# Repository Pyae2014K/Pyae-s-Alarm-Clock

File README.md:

# Pyae-s-Alarm-Clock

My alarm clock is an alarm clock with 6 keys, a TFT screen, and a buzzer.

It serves as an alarm clock that I can use every day to wake up on time for school.

## Features:
- 2.25in TFT Screen
- Buzzer for alarm
- 6 keys to do alarm things

## CAD Model
Everything fits together using 8 M3 Bolts and heatset inserts.

It has 2 different pieces, the Case and the Plate.

The model was made in Shapr 3D

##PCB
My PCB was made using KiCad
Schematic

PCB

I used the footprints that were shown in the guide.

## Firmware
This alarm clock uses Arduino IDE
It does alarm clock things.

## BOM:
Here is everything you will need to make this alarm clock

6x Charry MX Switches
6x DSA Keycaps
8x M3x5x4 Heatset inserts
8x M3x16mm SHCS Bolts
6x 1N4148 DO-35 Diodes.
1x 2.25in TFT Screen
1x XIAO ESP32C3
1x Case (2 printed parts)

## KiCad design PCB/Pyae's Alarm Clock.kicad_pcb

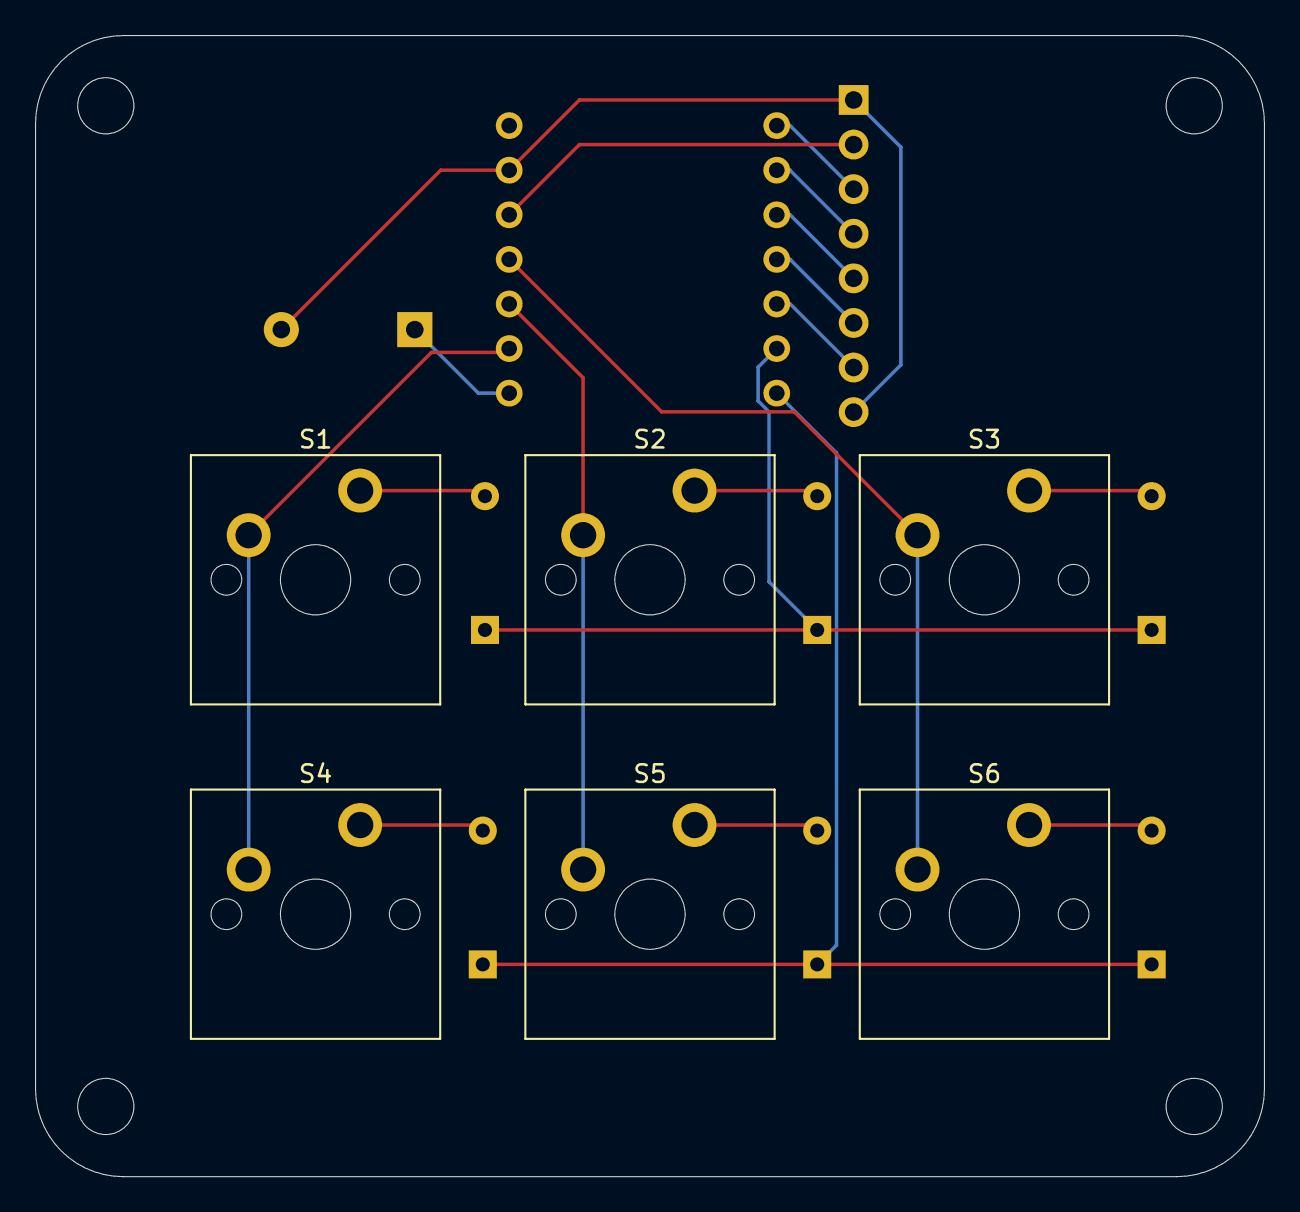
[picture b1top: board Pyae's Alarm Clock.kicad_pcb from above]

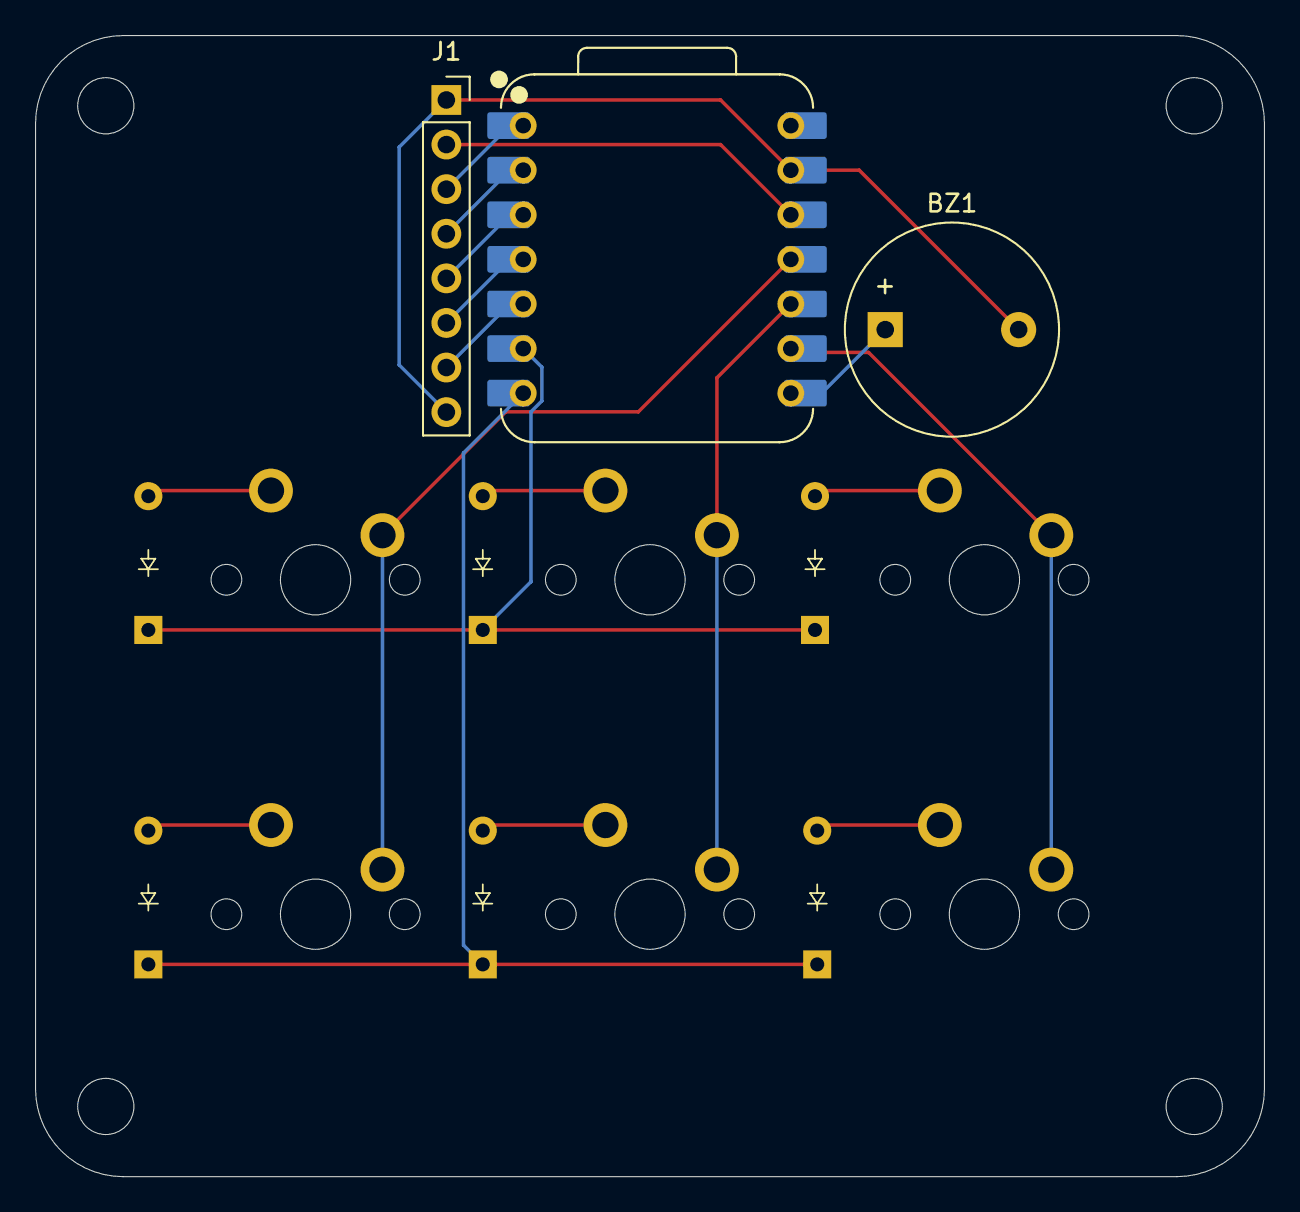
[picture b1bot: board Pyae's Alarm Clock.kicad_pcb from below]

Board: 2 copper layers, 70.0 x 65.0 mm, 19 parts (9 on the bottom side), 19 nets.

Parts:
BZ1: Buzzer; Buzzer_12x9.5RM7.6
D1, D2, D3, D4, D5, D6: Diode_DO-35
H1, H2, H3, H4: MountingHole; MountingHole_3.2mm_M3
J1: Conn_01x08_Pin; PinSocket_1x08_P2.54mm_Vertical
S1, S2, S3, S4, S5, S6: MX_PCB_1.00u
U1: XIAO-ESP32-C3-SMD; XIAO-ESP32-C3-DIP

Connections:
+3.3V: J1.2, U1.12 (3V3_OUT)
/CS: J1.7, U1.5 (D4)
/Col0: S1.1, S4.1, U1.9 (D8)
/Col1: S2.1, S5.1, U1.10 (D9/BOOT)
/Col2: S3.1, S6.1, U1.11 (D10)
/DC: J1.6, U1.4 (D3)
/RST: J1.5, U1.3 (D2)
/Row0: D1.1 (K), D2.1 (K), D3.1 (K), U1.6 (D5)
/Row1: D4.1 (K), D5.1 (K), D6.1 (K), U1.7 (D6)
/SCL: J1.3, U1.1 (D0)
/SDA: J1.4, U1.2 (D1)
GND: BZ1.2 (-), J1.1, J1.8, U1.13 (GND)
unnamed: BZ1.1 (+), U1.8 (D7)
unnamed: D1.2 (A), S1.2
unnamed: D2.2 (A), S2.2
unnamed: D3.2 (A), S3.2
unnamed: D4.2 (A), S4.2
unnamed: D5.2 (A), S5.2
unnamed: D6.2 (A), S6.2

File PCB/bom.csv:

Designator,Footprint,Quantity,Value,LCSC Part #
BZ1,Buzzer_12x9.5RM7.6,1,Buzzer,
"D1, D2, D3, D4, D5, D6",Diode_DO-35,6,~,
J1,PinSocket_1x08_P2.54mm_Vertical,1,Conn_01x08_Pin,
"S1, S2, S3, S4, S5, S6",MX_PCB_1.00u,6,~,
U1,XIAO-ESP32-C3-DIP,1,XIAO-ESP32-C3-SMD,

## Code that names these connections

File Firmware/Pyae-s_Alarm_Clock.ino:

#include <Adafruit_GFX.h>
#include <Adafruit_ST7789.h>
#include <SPI.h>
#include <WiFi.h>
#include "time.h"

const char* ssid = "your-wifi-name";
const char* password = "your-wifi-password";

// --- Display pins ---
#define TFT_SCLK 0
#define TFT_MOSI 1
#define TFT_RST 2
#define TFT_DC 3
#define TFT_CS 4
// BL hardwired to GND (active-low display, always on) — no GPIO needed.

// --- Matrix pins (2 rows x 3 cols = 6 switches) ---
#define ROW0 5
#define ROW1 6
#define COL0 8
#define COL1 9
#define COL2 10

// --- Buzzer ---
#define BUZZER_PIN 7

// setOffsets() isn't public on the base class, so expose it via a subclass
class MyST7789 : public Adafruit_ST7789 {
public:
  MyST7789(int8_t cs, int8_t dc, int8_t mosi, int8_t sclk, int8_t rst)
    : Adafruit_ST7789(cs, dc, mosi, sclk, rst) {}
  void setOffsets(uint8_t col, uint8_t row) {
    _colstart = _colstart2 = col;
    _rowstart = _rowstart2 = row;
  }
};

MyST7789 Pyae(TFT_CS, TFT_DC, TFT_MOSI, TFT_SCLK, TFT_RST);

// --- Modes ---
enum Mode { MODE_CLOCK, MODE_SET_TIME, MODE_SET_ALARM, MODE_SET_TIMER };
Mode currentMode = MODE_CLOCK;

// --- Alarm / timer state ---
int alarmHour = 7;
int alarmMinute = 0;
bool alarmEnabled = true;
bool alarmRinging = false;

long timerSecondsRemaining = 0;
bool timerRunning = false;
unsigned long lastTimerTick = 0;

// --- Manual time-set staging values (used while in MODE_SET_TIME) ---
int setHour = 0;
int setMinute = 0;

int lastDisplayedMinute = -1;

// --- Matrix scanning with simple debounce ---
const int rowPins[2] = { ROW0, ROW1 };
const int colPins[3] = { COL0, COL1, COL2 };

int lastSwitchPressed = 0; // 0 = none, 1-6 = SW1-SW6
unsigned long lastDebounceTime = 0;
const unsigned long debounceDelay = 50;

// Returns 1-6 for SW1-SW6 if a NEW press is detected this call, else 0.
// SW1,SW2,SW3 = Row0 x Col0,Col1,Col2
// SW4,SW5,SW6 = Row1 x Col0,Col1,Col2
int scanMatrixForNewPress() {
  int pressed = 0;

  for (int r = 0; r < 2; r++) {
    // Drive only this row LOW, others stay HIGH (input pull-up columns read LOW when pressed)
    digitalWrite(rowPins[0], HIGH);
    digitalWrite(rowPins[1], HIGH);
    digitalWrite(rowPins[r], LOW);
    delayMicroseconds(5); // let the line settle

    for (int c = 0; c < 3; c++) {
      if (digitalRead(colPins[c]) == LOW) {
        pressed = (r * 3) + c + 1; // 1-6
      }
    }
  }
  digitalWrite(rowPins[0], HIGH);
  digitalWrite(rowPins[1], HIGH);

  if (pressed != lastSwitchPressed) {
    lastDebounceTime = millis();
  }

  int result = 0;
  if ((millis() - lastDebounceTime) > debounceDelay) {
    if (pressed != 0 && lastSwitchPressed == 0) {
      result = pressed; // new press confirmed after debounce
    }
  }
  lastSwitchPressed = pressed;
  return result;
}

void drawCentered(const char* text) {
  Pyae.fillScreen(ST77XX_BLACK);
  Pyae.setCursor(0, 0);
  Pyae.setTextColor(ST77XX_WHITE);
  Pyae.setTextSize(6);
  Pyae.print(text);
}

void ringBuzzer(bool on) {
  digitalWrite(BUZZER_PIN, on ? HIGH : LOW);
}

void setup() {
  Serial.begin(115200);

  pinMode(ROW0, OUTPUT);
  pinMode(ROW1, OUTPUT);
  pinMode(COL0, INPUT_PULLUP);
  pinMode(COL1, INPUT_PULLUP);
  pinMode(COL2, INPUT_PULLUP);
  digitalWrite(ROW0, HIGH);
  digitalWrite(ROW1, HIGH);

  pinMode(BUZZER_PIN, OUTPUT);
  digitalWrite(BUZZER_PIN, LOW);

  Pyae.init(76, 284);
  Pyae.setOffsets(82, 18);
  Pyae.invertDisplay(false);
  Pyae.setRotation(1);
  Pyae.fillScreen(ST77XX_BLACK);
  Serial.println("TFT Initialized!");

  WiFi.begin(ssid, password);
  while (WiFi.status() != WL_CONNECTED) { delay(500); }

  configTime(0, 0, "pool.ntp.org");
  setenv("TZ", "PST8PDT,M3.2.0,M11.1.0", 1);
  tzset();
}

void loop() {
  struct tm timeinfo;
  bool haveTime = getLocalTime(&timeinfo);

  int pressedSwitch = scanMatrixForNewPress();

  // --- Handle switch presses ---
  if (pressedSwitch == 1) { // SW1: Stop alarm
    alarmRinging = false;
    ringBuzzer(false);
    if (timerRunning && timerSecondsRemaining <= 0) timerRunning = false;
    currentMode = MODE_CLOCK;
  } else if (pressedSwitch == 2) { // SW2: Timer -> set timer duration mode
    currentMode = MODE_SET_TIMER;
  } else if (pressedSwitch == 3) { // SW3: Change time -> set clock mode
    if (haveTime) {
      setHour = timeinfo.tm_hour;
      setMinute = timeinfo.tm_min;
    }
    currentMode = MODE_SET_TIME;
  } else if (pressedSwitch == 4) { // SW4: Set alarm mode
    currentMode = MODE_SET_ALARM;
  } else if (pressedSwitch == 5) { // SW5: Up
    if (currentMode == MODE_SET_TIME) {
      setHour = (setHour + 1) % 24;
    } else if (currentMode == MODE_SET_ALARM) {
      alarmHour = (alarmHour + 1) % 24;
    } else if (currentMode == MODE_SET_TIMER) {
      timerSecondsRemaining += 60; // add a minute per press
    }
  } else if (pressedSwitch == 6) { // SW6: Down
    if (currentMode == MODE_SET_TIME) {
      setHour = (setHour + 23) % 24;
    } else if (currentMode == MODE_SET_ALARM) {
      alarmHour = (alarmHour + 23) % 24;
    } else if (currentMode == MODE_SET_TIMER) {
      timerSecondsRemaining = max(0L, timerSecondsRemaining - 60);
    }
  }

  // --- Alarm check (only in clock mode, only once per minute) ---
  if (haveTime && currentMode == MODE_CLOCK && alarmEnabled && !alarmRinging) {
    if (timeinfo.tm_hour == alarmHour && timeinfo.tm_min == alarmMinute && timeinfo.tm_sec == 0) {
      alarmRinging = true;
    }
  }
  if (alarmRinging) {
    ringBuzzer((millis() / 500) % 2 == 0); // simple on/off beep pattern
  }

  // --- Timer countdown ---
  if (timerRunning && millis() - lastTimerTick >= 1000) {
    lastTimerTick = millis();
    timerSecondsRemaining--;
    if (timerSecondsRemaining <= 0) {
      timerSecondsRemaining = 0;
      timerRunning = false;
      alarmRinging = true; // reuse the same ringing/dismiss logic
    }
  }

  // --- Display ---
  char buf[16];
  switch (currentMode) {
    case MODE_CLOCK:
      if (haveTime && timeinfo.tm_min != lastDisplayedMinute) {
        lastDisplayedMinute = timeinfo.tm_min;
        strftime(buf, sizeof(buf), "%H:%M", &timeinfo);
        drawCentered(buf);
      }
      break;
    case MODE_SET_TIME:
      snprintf(buf, sizeof(buf), "%02d:%02d", setHour, setMinute);
      drawCentered(buf);
      break;
    case MODE_SET_ALARM:
      snprintf(buf, sizeof(buf), "A%02d:%02d", alarmHour, alarmMinute);
      drawCentered(buf);
      break;
    case MODE_SET_TIMER:
      snprintf(buf, sizeof(buf), "T%02ld:%02ld", timerSecondsRemaining / 60, timerSecondsRemaining % 60);
      drawCentered(buf);
      break;
  }

  delay(20); // keep matrix scanning responsive without hammering the CPU
}
